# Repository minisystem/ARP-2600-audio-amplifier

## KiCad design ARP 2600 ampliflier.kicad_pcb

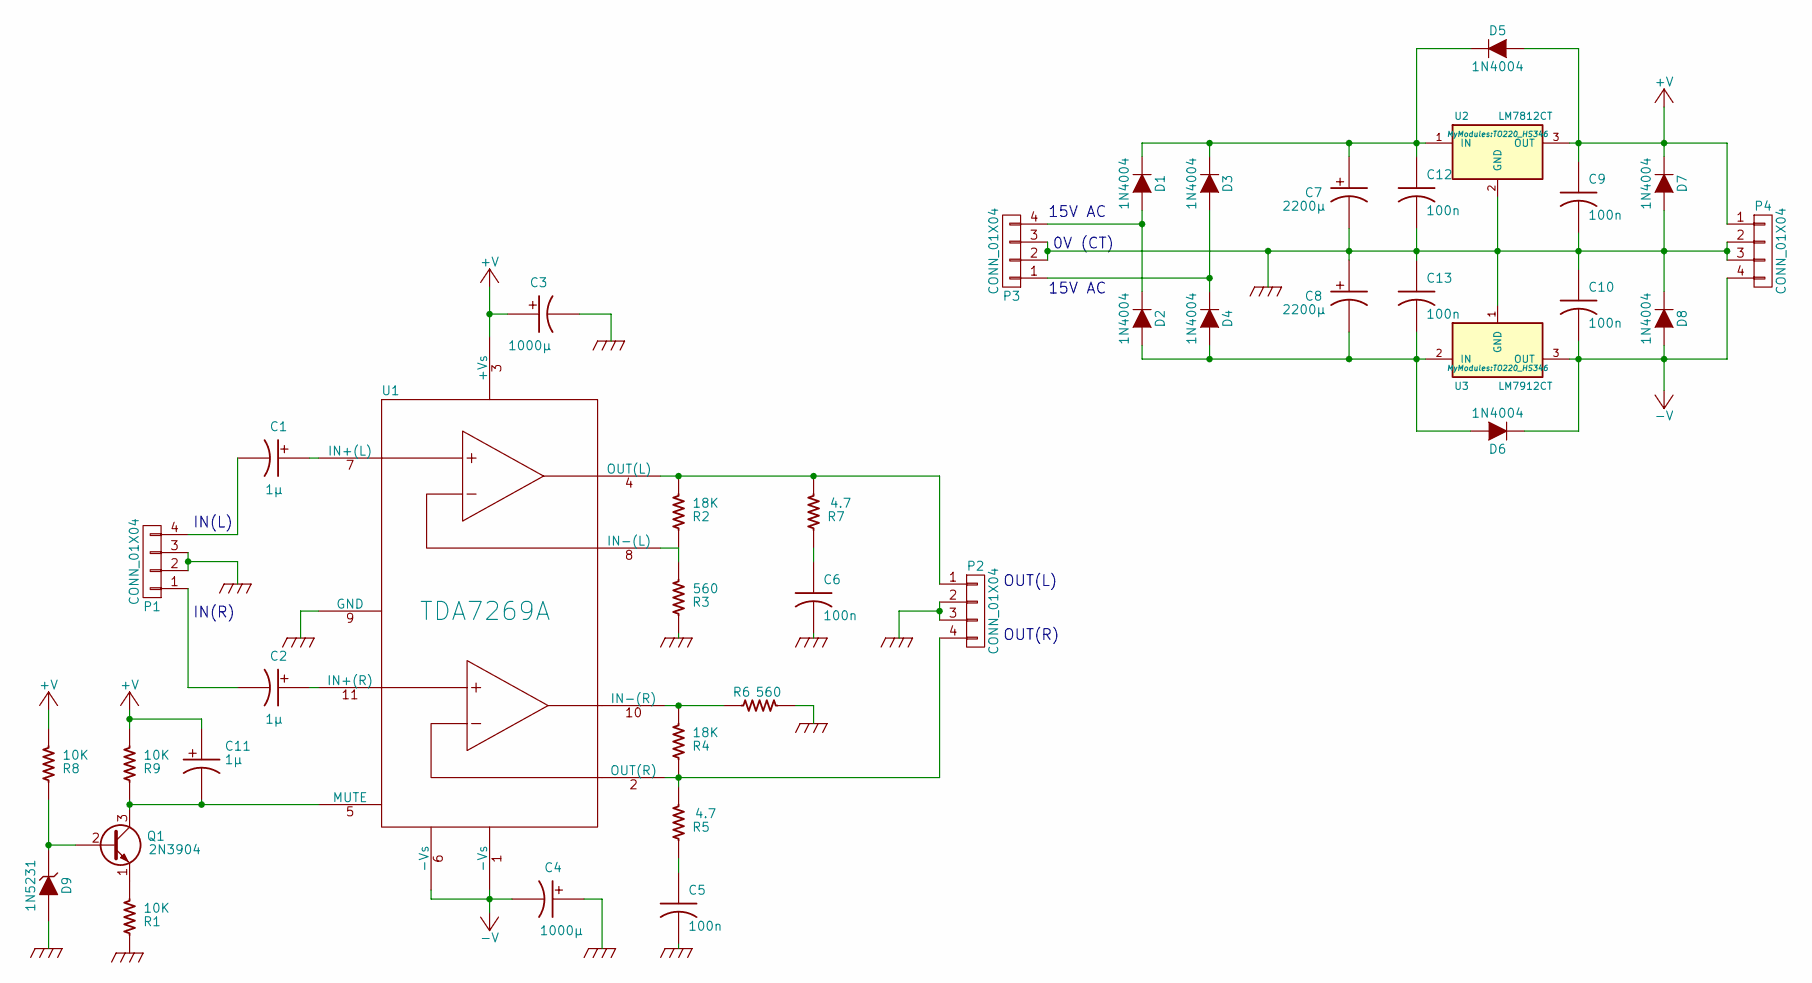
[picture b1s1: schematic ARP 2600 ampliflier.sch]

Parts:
C1, C2, C11: 1µ; 2MM-POL-CAP
C3, C4: 1000µ; 5MM-POL-CAP
C5, C6, C9, C10, C12, C13: 100n; C_Disc_D6_P5
C7, C8: 2200µ; 5MM-POL-CAP
D1, D2, D3, D4, D5, D6, D7, D8: 1N4004; Diode-DO-41
D9: 1N5231; Diode_DO-35_SOD27_Horizontal_RM10
P1, P2, P3, P4: CONN_01X04; mpt_0,5%2f4-2,54
Q1: 2N3904
R1, R8, R9: 10K; Resistor_Horizontal_RM10mm
R2, R4: 18K; Resistor_Horizontal_RM10mm
R3, R6: 560; Resistor_Horizontal_RM10mm
R5, R7: 4.7; Resistor_Horizontal_RM10mm
U1: TDA7269A; Multiwatt11-6400BG
U2: LM7812CT; TO220_HS346
U3: LM7912CT; TO220_HS346

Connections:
+V: C3.1 (+), C9.1, C11.1 (+), D5.2 (A), D7.1 (K), P4.1, R8.1, R9.1, U1.3 (+Vs), U2.3 (OUT)
-V: C4.2 (-), C10.2, D6.1 (K), D8.2 (A), P4.4, U1.1 (-Vs), U1.6 (-Vs), U3.3 (OUT)
GND: C3.2 (-), C4.1 (+), C5.2, C6.2, C7.2 (-), C8.1 (+), C9.2, C10.1, C12.2, C13.1, D7.2 (A), D8.1 (K), D9.2 (A), P1.2, P1.3, P2.2, P2.3, P3.2, P3.3, P4.2, P4.3, R1.2, R3.2, R6.1, U1.9 (GND), U2.2 (GND), U3.1 (GND)
unnamed: C1.1 (+), U1.7 (IN+(L))
unnamed: C1.2 (-), P1.4
unnamed: C2.1 (+), U1.11 (IN+(R))
unnamed: C2.2 (-), P1.1
unnamed: C5.1, R5.2
unnamed: C6.1, R7.2
unnamed: C11.2 (-), Q1.3 (C), R9.2, U1.5 (MUTE)
unnamed: C7.1 (+), C12.1, D1.1 (K), D3.1 (K), D5.1 (K), U2.1 (IN)
unnamed: C8.2 (-), C13.2, D2.2 (A), D4.2 (A), D6.2 (A), U3.2 (IN)
unnamed: D1.2 (A), D2.1 (K), P3.4
unnamed: D3.2 (A), D4.1 (K), P3.1
unnamed: D9.1 (K), Q1.2 (B), R8.2
unnamed: P2.1, R2.1, R7.1, U1.4 (OUT(L))
unnamed: P2.4, R4.2, R5.1, U1.2 (OUT(R))
unnamed: Q1.1 (E), R1.1
unnamed: R2.2, R3.1, U1.8 (IN-(L))
unnamed: R4.1, R6.2, U1.10 (IN-(R))

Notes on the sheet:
IN(L)
IN(R)
OUT(L)
OUT(R)
15V AC
0V (CT)

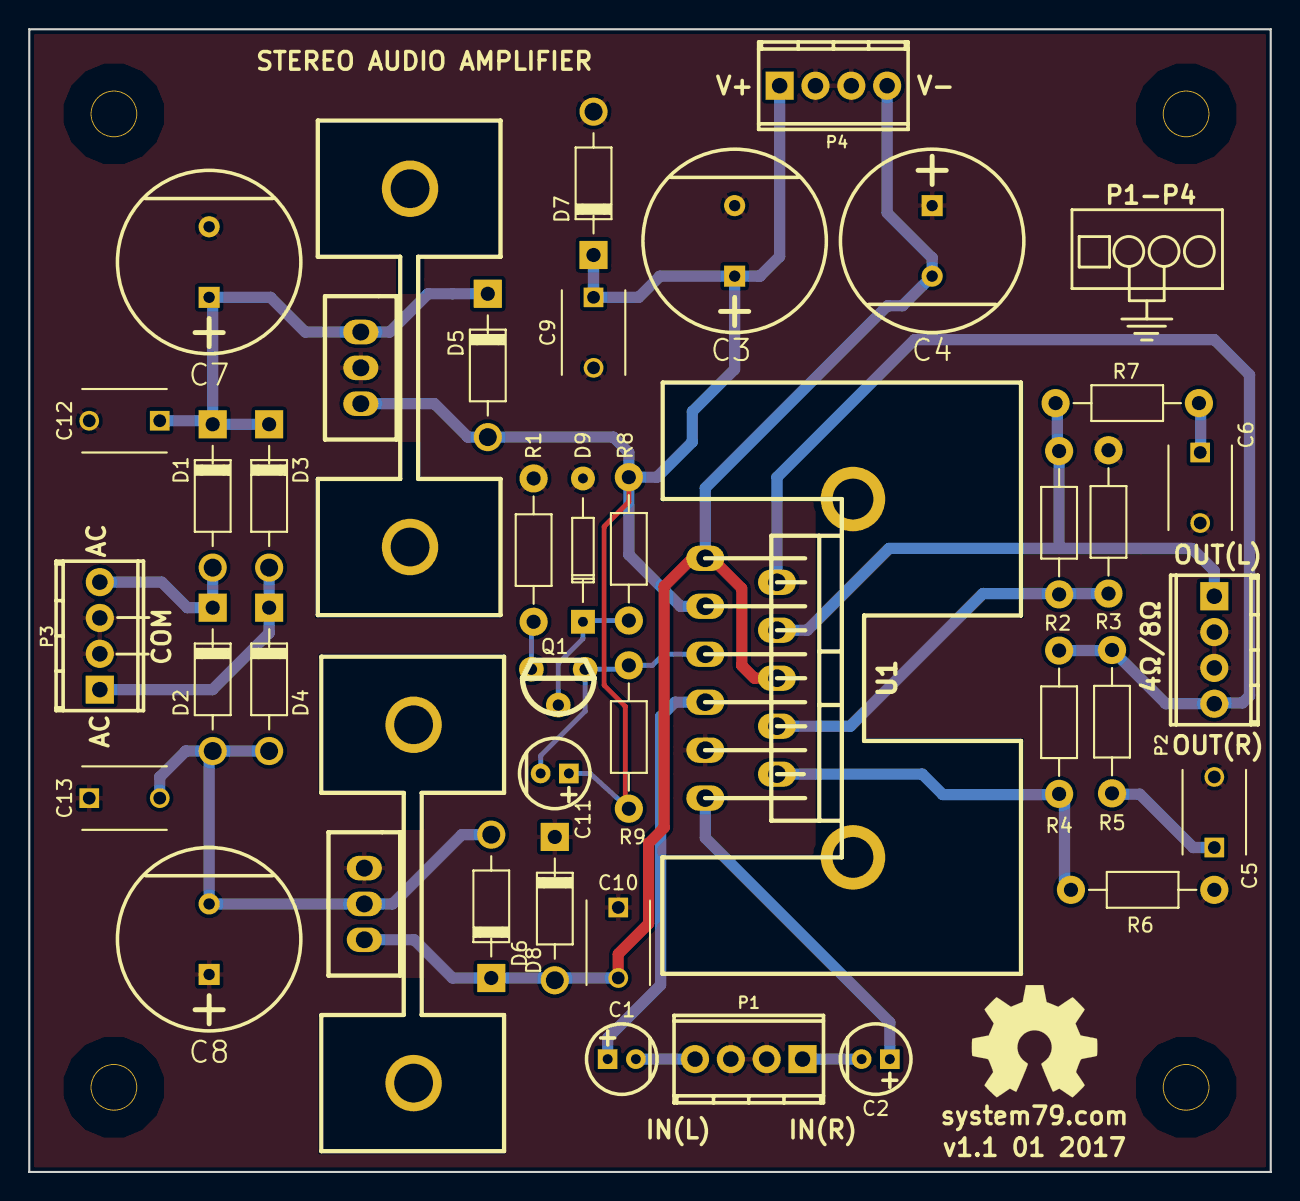
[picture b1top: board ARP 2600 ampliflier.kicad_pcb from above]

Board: 2 copper layers, 88.0 x 81.0 mm, 43 parts (0 on the bottom side), 20 nets.

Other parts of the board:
HOLE-0.125-INCH, HOLE-0.125-INCH#2, HOLE-0.125-INCH#3, HOLE-0.125-INCH#4: VAL**; HOLE-0.125-INCH

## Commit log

2016-12-14 footprints assigned, netlist imported into pcbnew
2016-12-14 routed
2016-12-17 few tweaks, exported .png of 3D view
2016-12-17 added standby/mute control during power up, generated gerbers
2016-12-18 ready to order
2016-12-31 fixed pintout error with T0-220 footprints, fix Q1 footprint pintout error, add keepout zones to heatsink landing areas on top copper
2017-01-05 fixed another mistake - two -Vs pins on amplifier you donut
2017-01-08 fixed. ready to order next revision
